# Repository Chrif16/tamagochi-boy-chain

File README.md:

# chamabochi
a little guy you can put on a chain that increases your swag tenfold but you have to take care of him. i made him as part fashion accessory part useful gadget that detects humidity and part fun game/fidget toy you can play with. 

# Features
you can pet him, play with him, feed him, shake him, put him to sleep etc and he'll make some cute expressions and animations custom made by me.
he comes equiped with a gyroscope and a humidity and temperature sensor so he can help you out too
he has two buttons on his hands to control his expressions and to see his stats plus you can control the menu by tilting the gyroscope. 

# First concept
i was inspired by the firmware part of the starbie project to make a mini pcb companion 

it turned out just like how i imagined it its so sick

# Schematics
he has really small components that i tried to fit in together so that i can wire them properly

# PCB
i struggeled a bit with making his outline in edge cuts but i think it turned out fine + the wiring is flawless.

# 3D model
i made it in two parts so you can assemble the pcb first then put it in the case and close the lid + it has a hole to fit a chain through

# BOM

| number of parts | part | link | price |
| :--- | :--- | :--- | :--- |
| 1 | XIAO esp32 C3 | https://www.aliexpress.us/item/3256813149598103.html?spm=a2g0o.productlist.main.2.4ef97845HoWqO5&algo_pvid=f953ac0a-0951-4d56-8cdf-6d64eb5ece76&algo_exp_id=f953ac0a-0951-4d56-8cdf-6d64eb5ece76-1&pdp_ext_f=%7B%22order%22%3A%226%22%2C%22eval%22%3A%221%22%2C%22fromPage%22%3A%22search%22%7D&pdp_npi=6%40dis%21USD%217.89%217.89%21%21%2152.58%2152.58%21%40212e377f17917507422854488e0d7c%2112000060888678592%21sea%21US%210%21ABX%211%210%21n_tag%3A-29910%3Bd%3Aa568ec5c%3Bm03_new_user%3A-29895&curPageLogUid=uryVSctWyLLP&utparam-url=scene%3Asearch%7Cquery_from%3A%7Cx_object_id%3A1005013335912855%7C_p_origin_prod%3A | $7.89  |
| 1 | battery enclosure | https://www.digikey.ch/en/products/detail/te-connectivity-linx/BAT-HLD-001/1577235 | 0.35$ |
| 1 | LIR2032 Rechargeable Coin Cell | https://www.aliexpress.us/item/3256812069497102.html?spm=a2g0o.productlist.main.1.3f0e5a248pwO0t&algo_pvid=a9fbbd37-0fdc-4540-8b97-3922637a8dc8&algo_exp_id=a9fbbd37-0fdc-4540-8b97-3922637a8dc8-0&pdp_ext_f=%7B%22order%22%3A%22635%22%2C%22eval%22%3A%221%22%2C%22fromPage%22%3A%22search%22%7D&pdp_npi=6%40dis%21USD%216.45%214.84%21%21%2142.94%2132.20%21%402141396c17917519901923494e0e01%2112000057904214106%21sea%21US%210%21ABX%211%210%21n_tag%3A-29910%3Bd%3Aa568ec5c%3Bm03_new_user%3A-29895&curPageLogUid=uMkBqYxxuqqm&utparam-url=scene%3Asearch%7Cquery_from%3A%7Cx_object_id%3A1005012255811854%7C_p_origin_prod%3A | $2.62 |
| 5 | pcb | jlcpcb | 10$ |
| 1 | 1.28 Inch Round TFT LCD Display Module | https://www.aliexpress.us/item/3256809268628610.html?gatewayAdapt=glo2usa4itemAdapt | $4.75 |
| 1 |  dht11 sensor | https://www.aliexpress.us/item/3256808886855570.html?spm=a2g0o.productlist.main.31.6bca604a6FzdjX&algo_pvid=1644d2b8-c5eb-4665-a242-8e46e69669c4&algo_exp_id=1644d2b8-c5eb-4665-a242-8e46e69669c4-28&pdp_ext_f=%7B%22order%22%3A%22462%22%2C%22eval%22%3A%221%22%2C%22fromPage%22%3A%22search%22%7D&pdp_npi=6%40dis%21USD%211.46%211.09%21%21%211.46%211.09%21%4021410daa17917515645302266e0ede%2112000047819045373%21sea%21US%210%21ABX%211%210%21n_tag%3A-29910%3Bd%3Aa568ec5c%3Bm03_new_user%3A-29895%3BpisId%3A5000000218165380&curPageLogUid=zRanVKnYU9sz&utparam-url=scene%3Asearch%7Cquery_from%3A%7Cx_object_id%3A1005009073170322%7C_p_origin_prod%3A | $1.46$ |
| 1 | mpu6050 | https://www.aliexpress.us/item/3256807803434052.html?spm=a2g0o.productlist.main.13.36e849223M5YiJ&algo_pvid=72591f86-c8de-4b78-bd96-5fab9a3d11d5&algo_exp_id=72591f86-c8de-4b78-bd96-5fab9a3d11d5-12&pdp_ext_f=%7B%22order%22%3A%222505%22%2C%22eval%22%3A%221%22%2C%22fromPage%22%3A%22search%22%7D&pdp_npi=6%40dis%21USD%212.09%211.09%21%21%2113.95%217.29%21%40212a6df517917517700347092e0d6d%2112000046422332178%21sea%21US%210%21ABX%211%210%21n_tag%3A-29910%3Bd%3Aa568ec5c%3Bm03_new_user%3A-29895%3BpisId%3A5000000218165385&curPageLogUid=lthkqjsFkiGO&utparam-url=scene%3Asearch%7Cquery_from%3A%7Cx_object_id%3A1005007989748804%7C_p_origin_prod%3A | $1.81 |
| 2 | cherry mx switches | https://www.aliexpress.us/item/3256811880813653.html?spm=a2g0o.productlist.main.1.2d044710fh0nZn&algo_pvid=0cd28c96-432d-43b2-874c-9a3962dca60e&algo_exp_id=0cd28c96-432d-43b2-874c-9a3962dca60e-0&pdp_ext_f=%7B%22order%22%3A%22299%22%2C%22eval%22%3A%221%22%2C%22fromPage%22%3A%22search%22%7D&pdp_npi=6%40dis%21USD%215.13%211.09%21%21%215.13%211.09%21%40212a6df517917522203607560e0e12%2112000057415897655%21sea%21US%210%21ABX%211%210%21n_tag%3A-29910%3Bd%3Aa568ec5c%3Bm03_new_user%3A-29895%3BpisId%3A5000000218165385&curPageLogUid=oSDRBrAhvjx1&utparam-url=scene%3Asearch%7Cquery_from%3A%7Cx_object_id%3A1005012067128405%7C_p_origin_prod%3A | 1.26$ |
| ? | PLA plastic for 3d printing |  | ?$ |
|  | total |  | >30.14$|

# How to build:

For screws and similar items, it is recommended to find the cheapest in your location. first 3d print all the parts in the cad folder except for the assembly, buy the pcb, flash the esp32, solder all the components on your pcb,charge your battery and put it in its spot, put your finished pcb inside the case and screw it shut and voila 
# Zine

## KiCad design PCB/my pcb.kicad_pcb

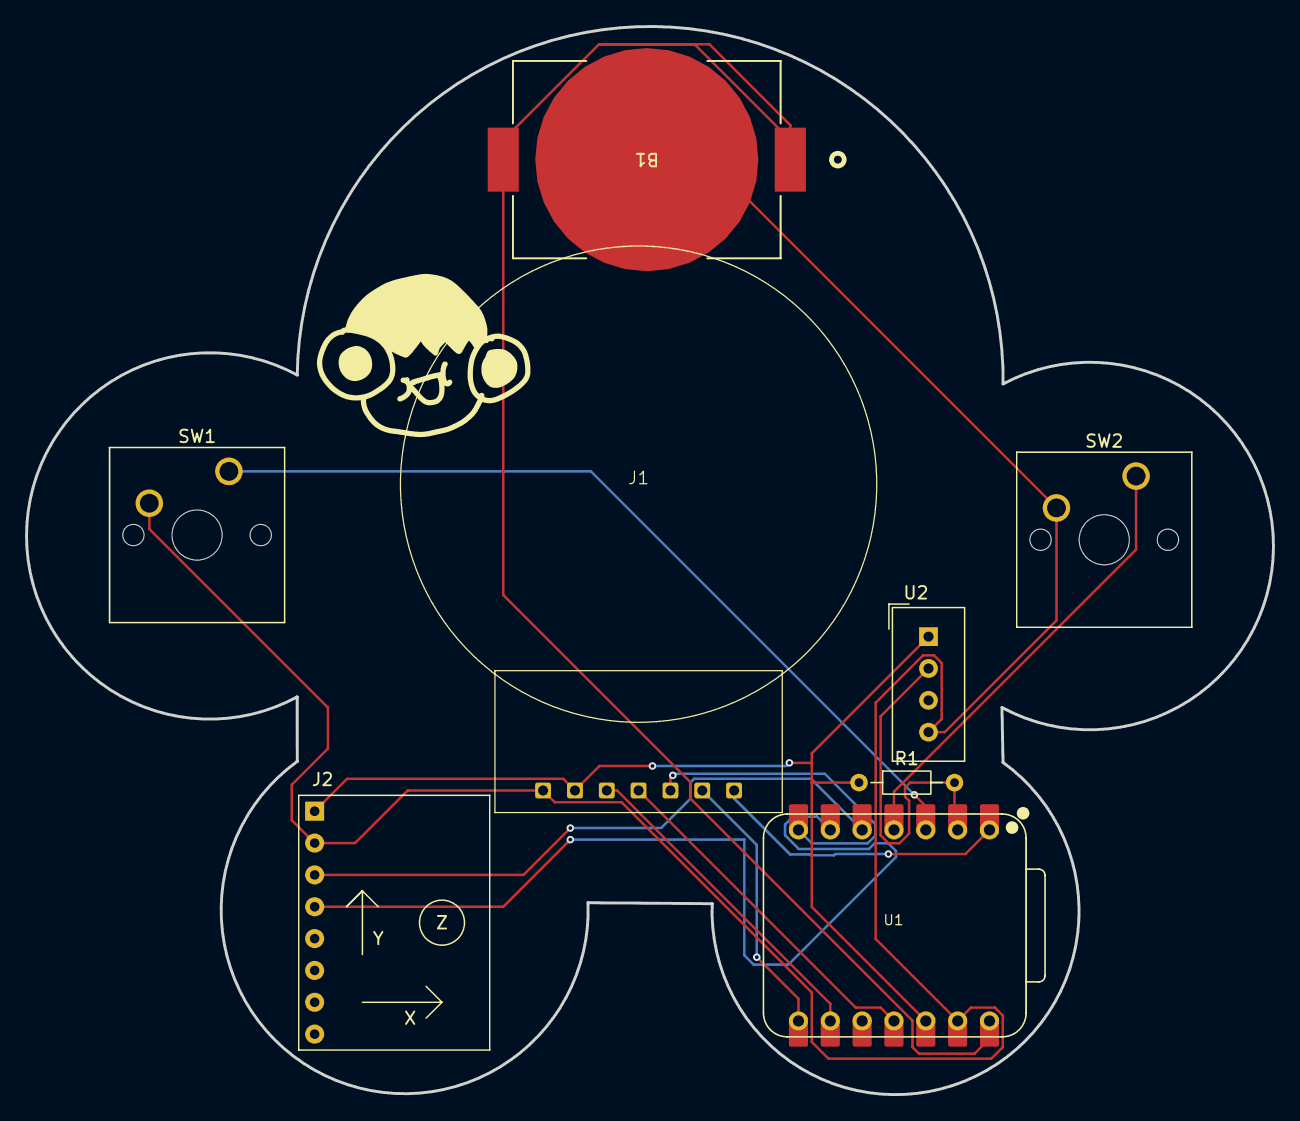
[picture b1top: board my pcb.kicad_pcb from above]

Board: 2 copper layers, 99.5 x 85.2 mm, 8 parts (0 on the bottom side), 13 nets.

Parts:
B1: BAT-HLD-001; BATT_HLDR_LNX
J1: Conn_01x07_Pin; 1.28 inch round TFT SPI 240x240
J2: Conn_01x08_Pin; MPU6050_Module
R1: 10K; R_Axial_DIN0204_L3.6mm_D1.6mm_P7.62mm_Horizontal
SW1, SW2: SW_Push; SW_Cherry_MX_1.00u_PCB
U1: XIAO-ESP32-C3-SMD; XIAO-ESP32-C6-DIP
U2: DHT11; Aosong_DHT11_5.5x12.0_P2.54mm

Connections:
+3.3V: J1.2, J2.1, R1.1, U1.12 (3V3_OUT), U2.1 (VDD)
+3V3: B1.1, B1.3
CS: J1.6, U1.8 (D7)
DC: J1.5, U1.7 (D6)
GND: B1.2, J1.1, J2.2, SW1.2, SW2.2, U1.13 (GND), U2.4 (GND)
MOSI: J1.4, U1.11 (D10)
RST: J1.7, U1.1 (D0)
SCK: J1.3, U1.9 (D8)
SCL: J2.3, U1.5 (D4)
SDA: J2.4, U1.6 (D5)
button 1: SW1.1, U1.3 (D2)
button 2: SW2.1, U1.4 (D3)
dht11 data: R1.2, U1.2 (D1), U2.2 (DATA)
